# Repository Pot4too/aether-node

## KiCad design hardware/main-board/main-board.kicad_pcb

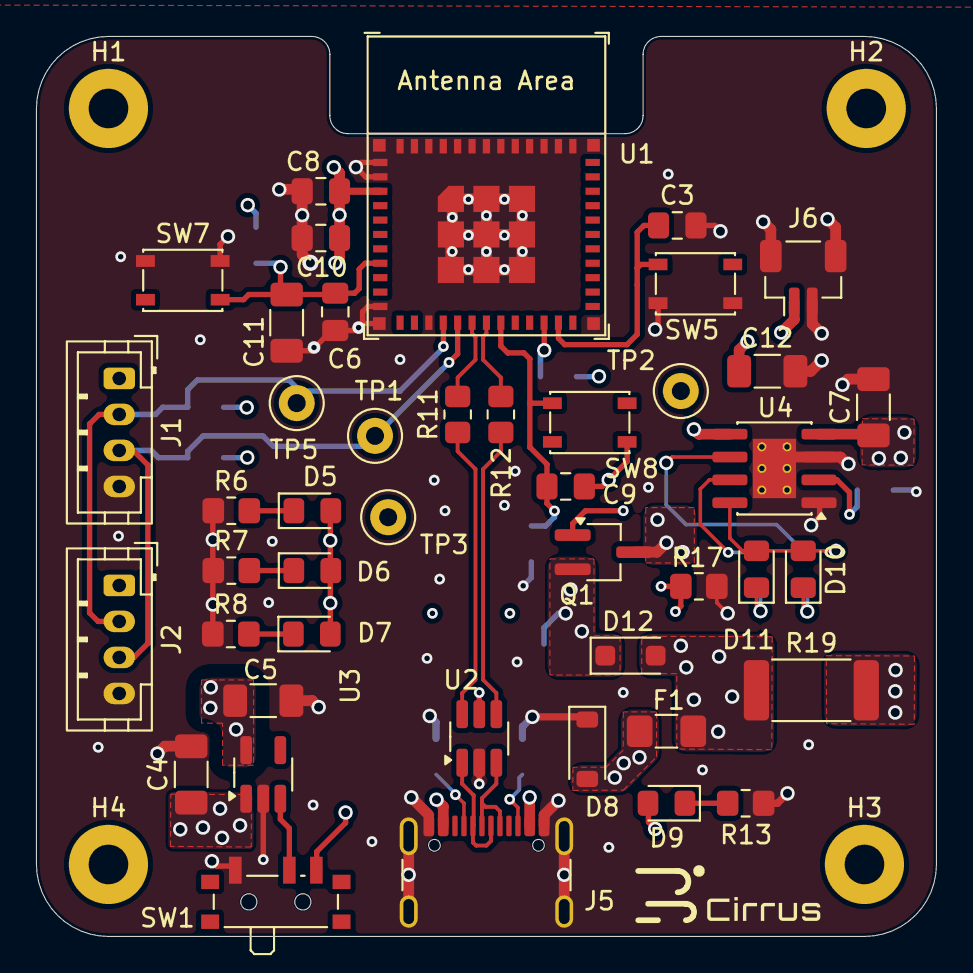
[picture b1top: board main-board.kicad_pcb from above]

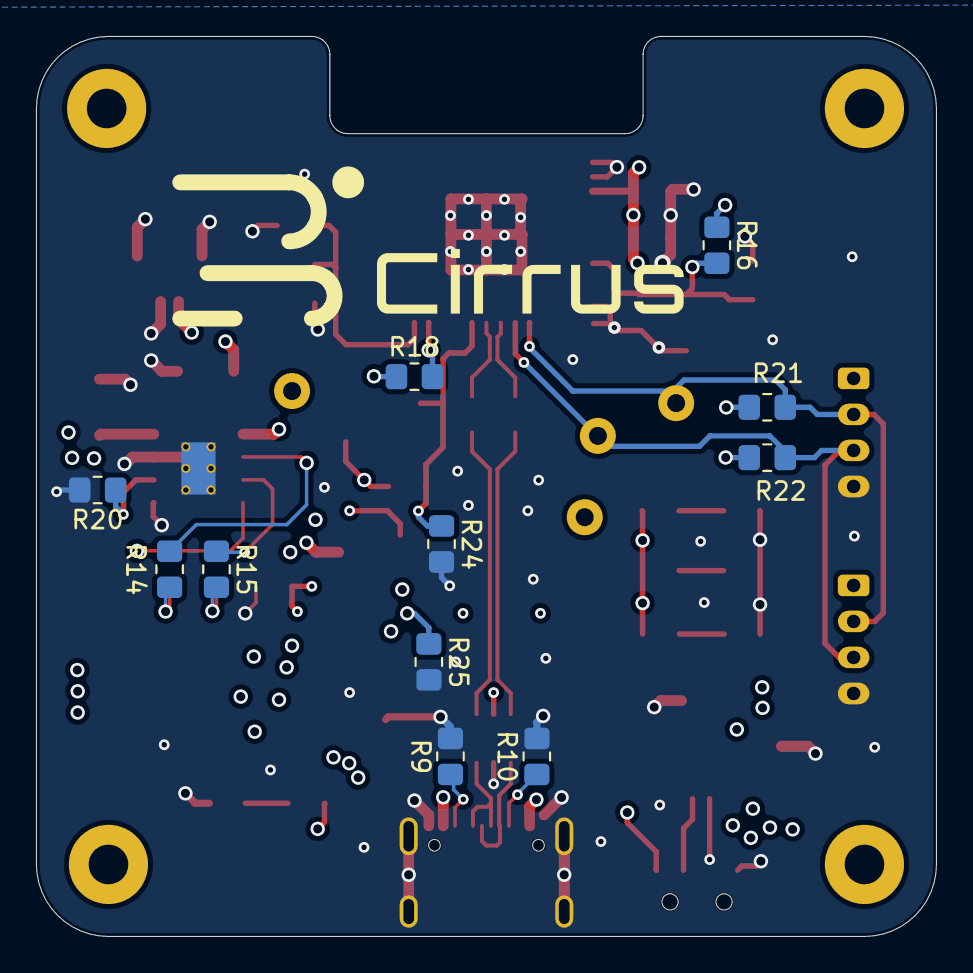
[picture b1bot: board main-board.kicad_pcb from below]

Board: 4 copper layers, 50.0 x 50.0 mm, 59 parts (11 on the bottom side), 31 nets.

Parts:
C3, C6, C9, C10: 100n; C_0805_2012Metric_Pad1.18x1.45mm_HandSolder
C4, C5, C11: 1u; C_1206_3216Metric_Pad1.33x1.80mm_HandSolder
C7, C12: 10u; C_1206_3216Metric_Pad1.33x1.80mm_HandSolder
C8: 22u; C_0805_2012Metric_Pad1.18x1.45mm_HandSolder
D5, D6, D9, D10: LED Green; LED_0805_2012Metric_Pad1.15x1.40mm_HandSolder
D7, D11: LED Red; LED_0805_2012Metric_Pad1.15x1.40mm_HandSolder
D8: FUXINSEMI SMF5.0CA; D_SOD-123
D12: MBR120LSFT1G; D_SOD-123F
F1: NSMD150/16; Fuse_1206_3216Metric_Pad1.42x1.75mm_HandSolder
H1, H2, H3, H4: MountingHole; MountingHole_2.2mm_M2_Pad
J1, J2: Conn_01x04_Socket; JST_PH_B4B-PH-K_1x04_P2.00mm_Vertical
J5: USB_C_Receptacle_USB2.0_16P; USB_C_Receptacle_GCT_USB4105-xx-A_16P_TopMnt_Horizontal
J6: Conn_01x02_MountingPin; JST_SH_BM02B-SRSS-TB_1x02-1MP_P1.00mm_Vertical
Q1: DMG2305UX; TSOT-23_HandSoldering
R6, R7, R8: 90; R_0805_2012Metric_Pad1.20x1.40mm_HandSolder
R9, R10, R20: 5.1k; R_0805_2012Metric_Pad1.20x1.40mm_HandSolder
R11, R12: 22; R_0805_2012Metric_Pad1.20x1.40mm_HandSolder
R13, R14, R15: 200; R_0805_2012Metric_Pad1.20x1.40mm_HandSolder
R16, R18, R24: 10k; R_0805_2012Metric_Pad1.20x1.40mm_HandSolder
R17, R25: 100k; R_0805_2012Metric_Pad1.20x1.40mm_HandSolder
R19: 0.4; R_2512_6332Metric_Pad1.40x3.35mm_HandSolder
R21, R22: 4.7k; R_0805_2012Metric_Pad1.20x1.40mm_HandSolder
SW1: C&K PCM12SMTR; SW_SPDT_PCM12
SW5, SW7, SW8: C&K PTS815SJM250SMTR LFS; SW_SPST_PTS810
TP1, TP2, TP3, TP5: TestPoint; TestPoint_Loop_D1.80mm_Drill1.0mm_Beaded
U1: ESP32-C6-MINI-1/U; ESP32-C6-MINI-1
U2: USBLC6-2SC6; SOT-23-6_Handsoldering
U3: AP2112K-3.3; SOT-23-5_HandSoldering
U4: TP4056-42-ESOP8; SOIC-8-1EP_3.9x4.9mm_P1.27mm_EP2.41x3.3mm_ThermalVias

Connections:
+3.3V: C5.1, C8.2, C9.1, C10.1, D5.2 (A), D6.2 (A), D7.2 (A), J1.1, J2.1, R16.1, R18.1, R21.1, R22.1, SW8.1, TP3.1 (1_1), U1.3 (3V3), U3.5 (VOUT)
+5V: D9.2 (A), D12.2 (A), F1.2, Q1.1 (G), R17.1, R19.1
/BAT+: C12.1, J6.1, Q1.3 (D), TP2.1 (1_1), U4.5 (BAT)
/BOOT: C3.1, SW5.1, U1.23 (GPIO9)
/EN: C6.2, C11.1, R16.2, SW7.2, U1.8 (EN/CHIP_PU)
/IO8: R18.2, U1.22 (GPIO8)
/IO14: C9.2, R24.1, SW8.2, U1.19 (GPIO14)
/LDO_IN: C4.1, D12.1 (K), Q1.2 (S), R25.1, SW1.3 (C), U3.1 (VIN)
/SCL: J1.3, J2.3, R22.2, TP1.1 (1_1), U1.16 (MTDO/GPIO7)
/SDA: J1.2, J2.2, R21.2, TP5.1 (1_1), U1.15 (MTCK/GPIO6/ADC1_CH6)
/USB+: R12.1, U1.18 (GPIO13/USB_D+)
/USB-: R11.2, U1.17 (GPIO12/USB_D-)
/USB_CONN_D+: J5.A6 (D+), J5.B6 (D+), U2.3 (I/O2)
/USB_CONN_D-: J5.A7 (D-), J5.B7 (D-), U2.1 (I/O1)
/USB_ESD_D+: R12.2, U2.4 (I/O2)
/USB_ESD_D-: R11.1, U2.6 (I/O1)
GND: C3.2, C4.2, C5.2, C6.1, C7.2, C8.1, C10.2, C11.2, C12.2, D8.1 (A1), J1.4, J2.4, J5.A1 (GND), J5.A12 (GND), J5.B1 (GND), J5.B12 (GND), J5.SH (SHIELD), J6.2, J6.MP (MountPin), R6.1, R7.1, R8.1, R9.2, R10.2, R13.2, R17.2, R20.2, R24.2, R25.2, SW1.1 (A), SW5.2, SW7.1, U1.1 (GND), U1.2 (GND), U1.11 (GND), U1.14 (GND), U1.36 (GND), U1.37 (GND), U1.38 (GND), U1.39 (GND), U1.40 (GND), U1.41 (GND), U1.42 (GND), U1.43 (GND), U1.44 (GND), U1.45 (GND), U1.46 (GND), U1.47 (GND), U1.48 (GND), U1.49 (GND), U1.50 (GND), U1.51 (GND), U1.52 (GND), U1.53 (GND), U2.2 (GND), U3.2 (GND), U4.1 (TEMP), U4.3 (GND), U4.9 (EPAD)
unnamed: D5.1 (K), R6.2
unnamed: D6.1 (K), R7.2
unnamed: D7.1 (K), R8.2
unnamed: D8.2 (A2), F1.1, J5.A4 (VBUS), J5.A9 (VBUS), J5.B4 (VBUS), J5.B9 (VBUS), U2.5 (VBUS)
unnamed: D9.1 (K), R13.1
unnamed: C7.1, D10.2 (A), D11.2 (A), R19.2, U4.4 (V_{CC}), U4.8 (CE)
unnamed: D10.1 (K), R14.2
unnamed: D11.1 (K), R15.2
unnamed: J5.A5 (CC1), R10.1
unnamed: J5.B5 (CC2), R9.1
unnamed: SW1.2 (B), U3.3 (EN)
unnamed: R20.1, U4.2 (PROG)
unnamed: R15.1, U4.7 (~CHRG)
unnamed: R14.1, U4.6 (~STDBY)

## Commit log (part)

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2026-06-27 Added default files
2026-06-27 Removed documentation files from tracking, will be replacing them with links
2026-06-27 Initialized PlatformIO in firmware directory
    firmware sub-directory contains its own .gitignore file
    platformio.ini is set for board ESP32-C6 Super Mini
2026-06-28 Test main file to see if board and setup works correctly
